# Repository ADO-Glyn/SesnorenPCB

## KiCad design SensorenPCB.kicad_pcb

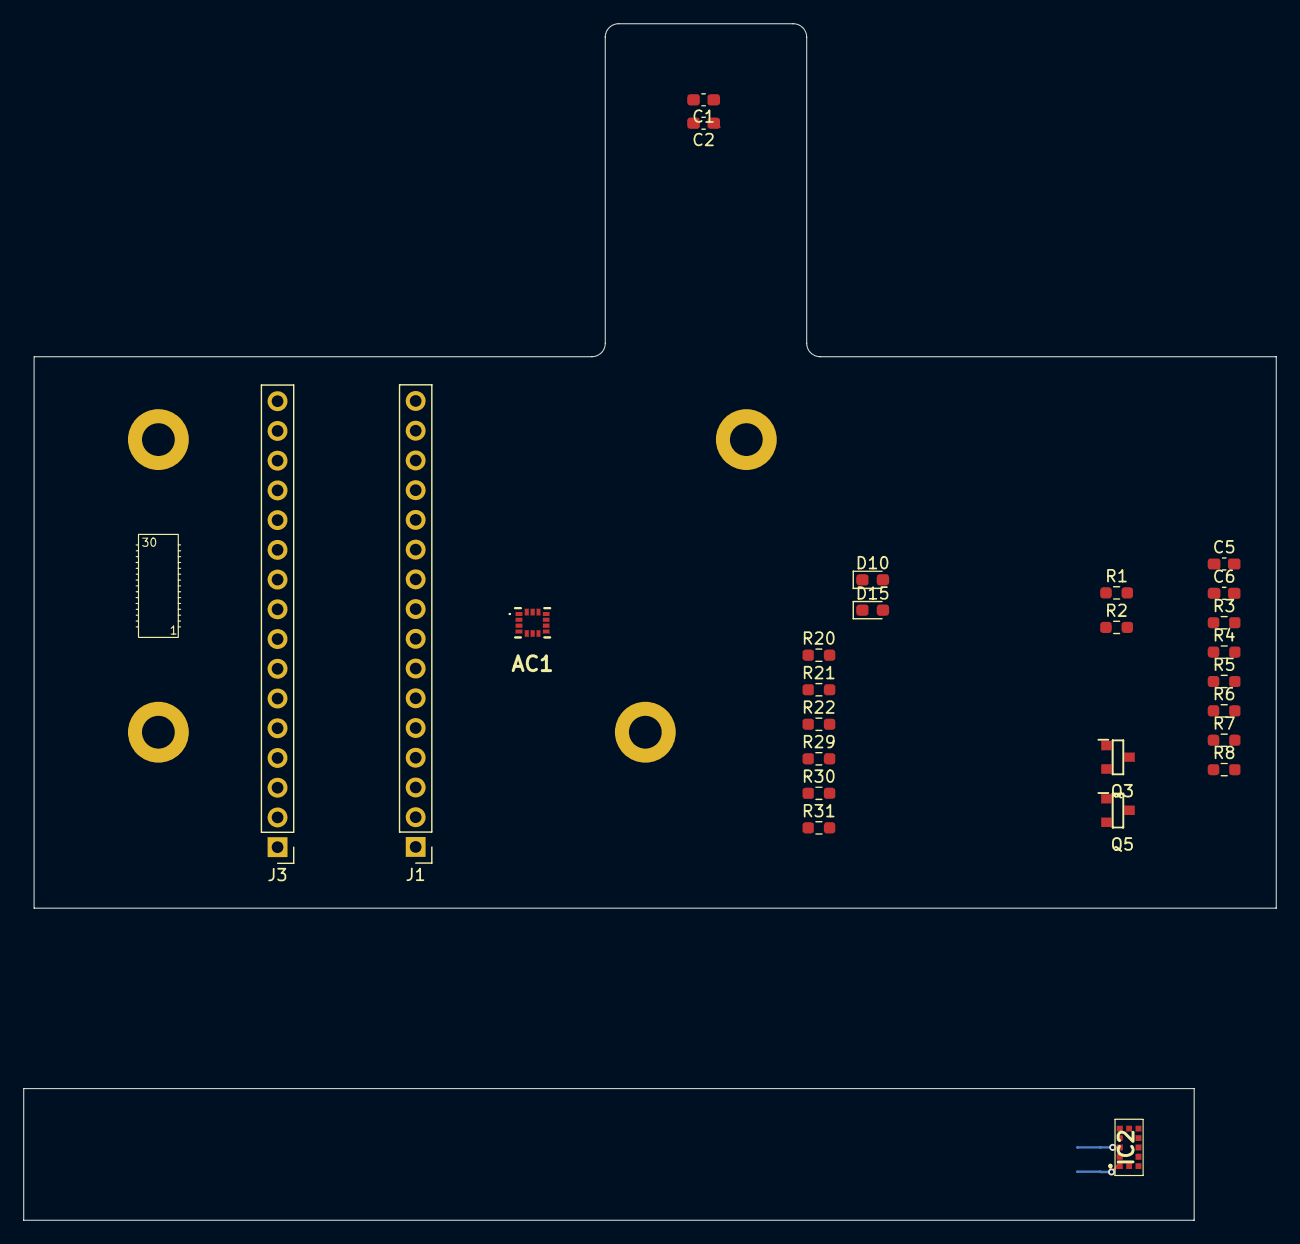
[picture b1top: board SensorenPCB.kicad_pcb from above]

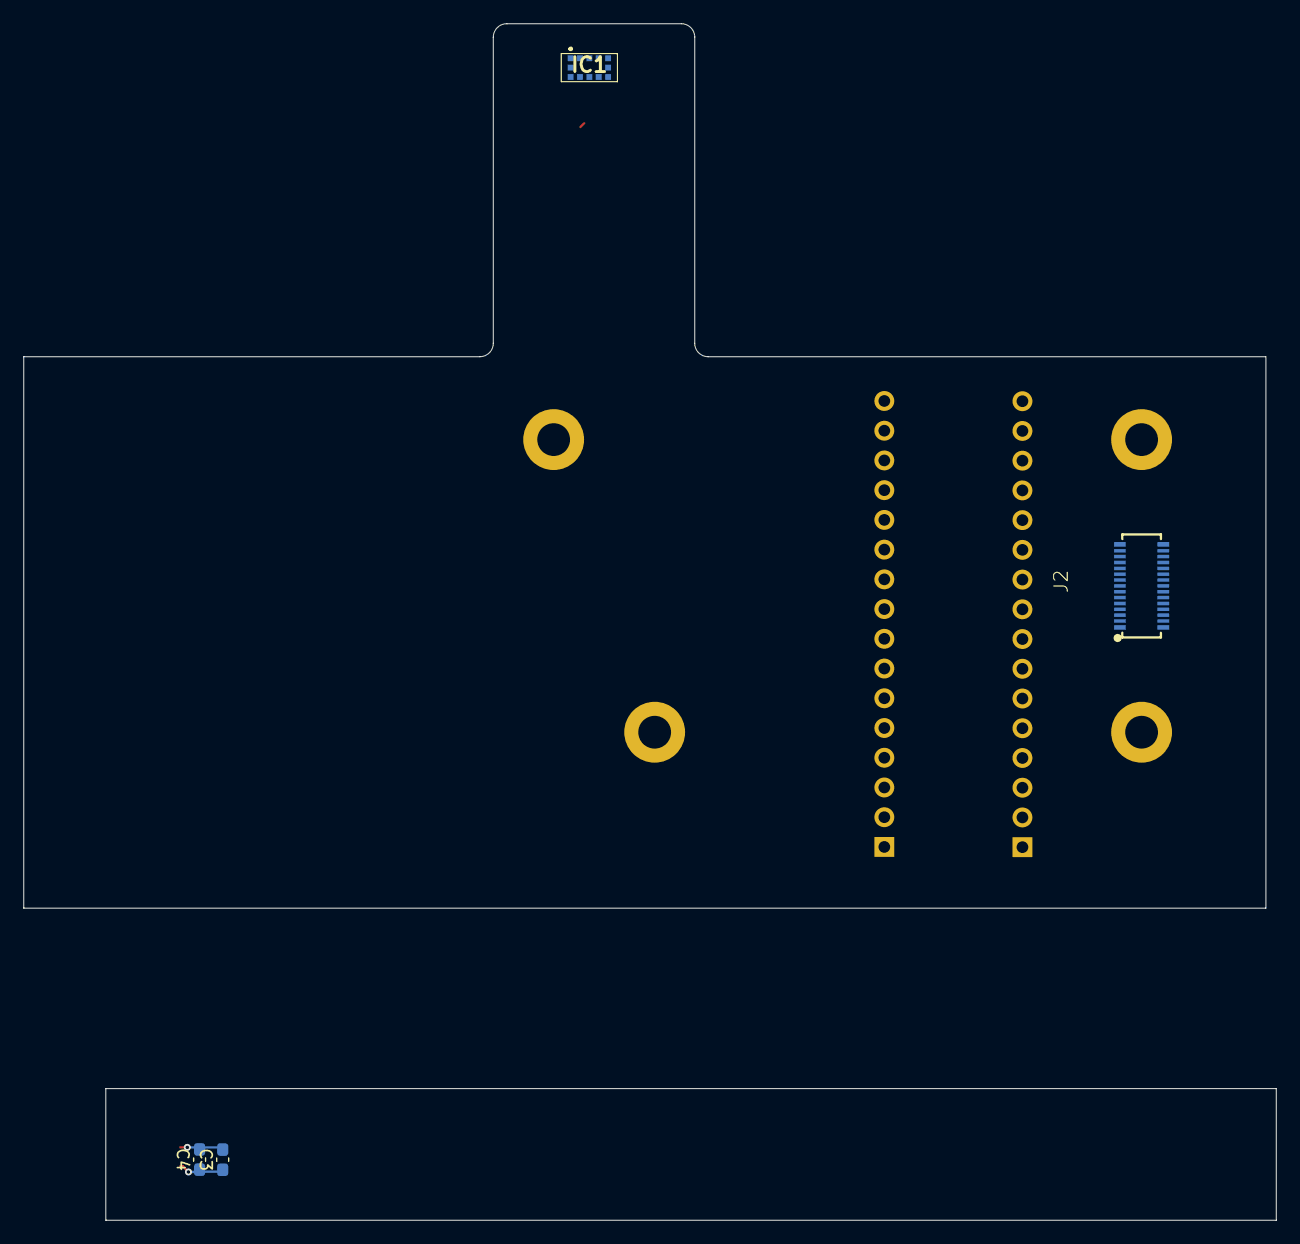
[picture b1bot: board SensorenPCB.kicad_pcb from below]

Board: 2 copper layers, 106.1 x 75.6 mm, 30 parts (3 on the bottom side), 35 nets.

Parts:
AC1: LSM6DSO
C1, C3: 4,7uF; C_0603_1608Metric_Pad1.08x0.95mm_HandSolder
C2, C4, C5, C6: 100nF; C_0603_1608Metric_Pad1.08x0.95mm_HandSolder
D10: green; LED_0603_1608Metric_Pad1.05x0.95mm_HandSolder
D15: red; LED_0603_1608Metric_Pad1.05x0.95mm_HandSolder
IC1, IC2: VL53L1CXV0FY_1; VL53L1CXV0FY1
J1, J3: Conn_01x16_Socket; PinHeader_1x16_P2.54mm_Vertical
J2: EDT_SE-Shield_027
Q3, Q5: BSS806N; SOT95P240X110-3N
R1, R2, R3, R4: 4.7k; R_0603_1608Metric_Pad0.98x0.95mm_HandSolder
R5, R6, R7, R8, R22, R31: 10k; R_0603_1608Metric_Pad0.98x0.95mm_HandSolder
R20: 68; R_0603_1608Metric_Pad0.98x0.95mm_HandSolder
R21, R30: 100; R_0603_1608Metric_Pad0.98x0.95mm_HandSolder
R29: 150; R_0603_1608Metric_Pad0.98x0.95mm_HandSolder

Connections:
+5V: D10.2 (A), D15.2 (A), J1.2, J2.1 (+5V), J3.2
/+3V3: AC1.5 (VDDIO), AC1.8 (VDD), AC1.11 (SDO_AUX_), AC1.12 (CS), C1.1, C2.1, C3.1, C4.1, C5.1, C6.1, IC1.1 (AVDDVCSEL), IC1.11 (AVDD), IC2.1 (AVDDVCSEL), IC2.11 (AVDD), J1.3, J2.3 (+3V3), J3.3, R1.1, R2.1, R3.1, R4.1, R5.1, R6.1, R7.1, R8.1
/ADC4_IN7: J2.26 (ADC4_IN7), J3.14
/DAC_OUT1: J2.28 (DAC_OUT1), J3.15
/GPIO1: J1.16, J2.29 (GPIO1), R21.1
/GPIO2: J2.30 (GPIO2), J3.16, R30.1
/I2C3_INT: IC1.7 (GPIO1), J1.6, J2.9 (I2C3_INT), R6.2
/I2C3_RST: IC1.5 (XSHUT), J1.7, J2.11 (I2C3_RST), R5.2
/I2C3_SCL: AC1.13 (SCL), IC1.10 (SCL), J1.4, J2.5 (I2C3_SCL), R2.2
/I2C3_SDA: AC1.14 (SDA), IC1.9 (SDA), J1.5, J2.7 (I2C3_SDA), R1.2
/I2C4_INT: IC2.7 (GPIO1), J2.10 (I2C4_INT), J3.6, R8.2
/I2C4_RST: IC2.5 (XSHUT), J2.12 (I2C4_RST), J3.7, R7.2
/I2C4_SCL: IC2.10 (SCL), J2.6 (I2C4_SCL), J3.4, R4.2
/I2C4_SDA: IC2.9 (SDA), J2.8 (I2C4_SDA), J3.5, R3.2
/SAI2_FS_A: J1.9, J2.15 (SAI2_FS_A)
/SAI2_MCLK_A: J1.10, J2.17 (SAI2_MCLK_A)
/SAI2_SCK_A: J1.8, J2.13 (SAI2_SCK_A)
/SAI2_SD_A: J1.11, J2.19 (SAI2_SD_A)
/SPI2_MISO: J2.18 (SPI2_MISO), J3.10
/SPI2_MOSI: J2.20 (SPI2_MOSI), J3.11
/SPI2_NSS: J2.14 (SPI2_NSS), J3.8
/SPI2_SCK: J2.16 (SPI2_SCK), J3.9
/USART3_RX: J2.24 (USART3_RX), J3.13
/USART3_TX: J2.22 (USART3_TX), J3.12
/USART6_CTS: AC1.9 (INT2), J1.15, J2.27 (USART6_CTS)
/USART6_RTS: AC1.4 (INT1_), J1.14, J2.25 (USART6_RTS)
/USART6_RX: J1.13, J2.23 (USART6_RX)
/USART6_TX: J1.12, J2.21 (USART6_TX)
GND: AC1.1 (SDO/SA0), AC1.2 (SDX), AC1.3 (SCX), AC1.6 (GND_1), AC1.7 (GND_2), C1.2, C2.2, C3.2, C4.2, C5.2, C6.2, IC1.2 (AVSSVCSEL), IC1.3 (GND), IC1.4 (GND2), IC1.6 (GND3), IC1.12 (GND4), IC2.2 (AVSSVCSEL), IC2.3 (GND), IC2.4 (GND2), IC2.6 (GND3), IC2.12 (GND4), J1.1, J2.2 (GND), J2.4 (GND), J3.1, Q3.2 (S), Q5.2 (S), R22.1, R31.1
unnamed: D10.1 (K), R20.1
unnamed: D15.1 (K), R29.1
unnamed: Q3.3 (D), R20.2
unnamed: Q3.1 (G), R21.2, R22.2
unnamed: Q5.3 (D), R29.2
unnamed: Q5.1 (G), R30.2, R31.2
